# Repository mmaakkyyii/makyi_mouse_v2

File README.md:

# マッキーマウスv2
これはマッキーマウスの基板用リポジトリです  
ソフトは[こちら](https://github.com/mmaakkyyii/makyi_mouse_FW)

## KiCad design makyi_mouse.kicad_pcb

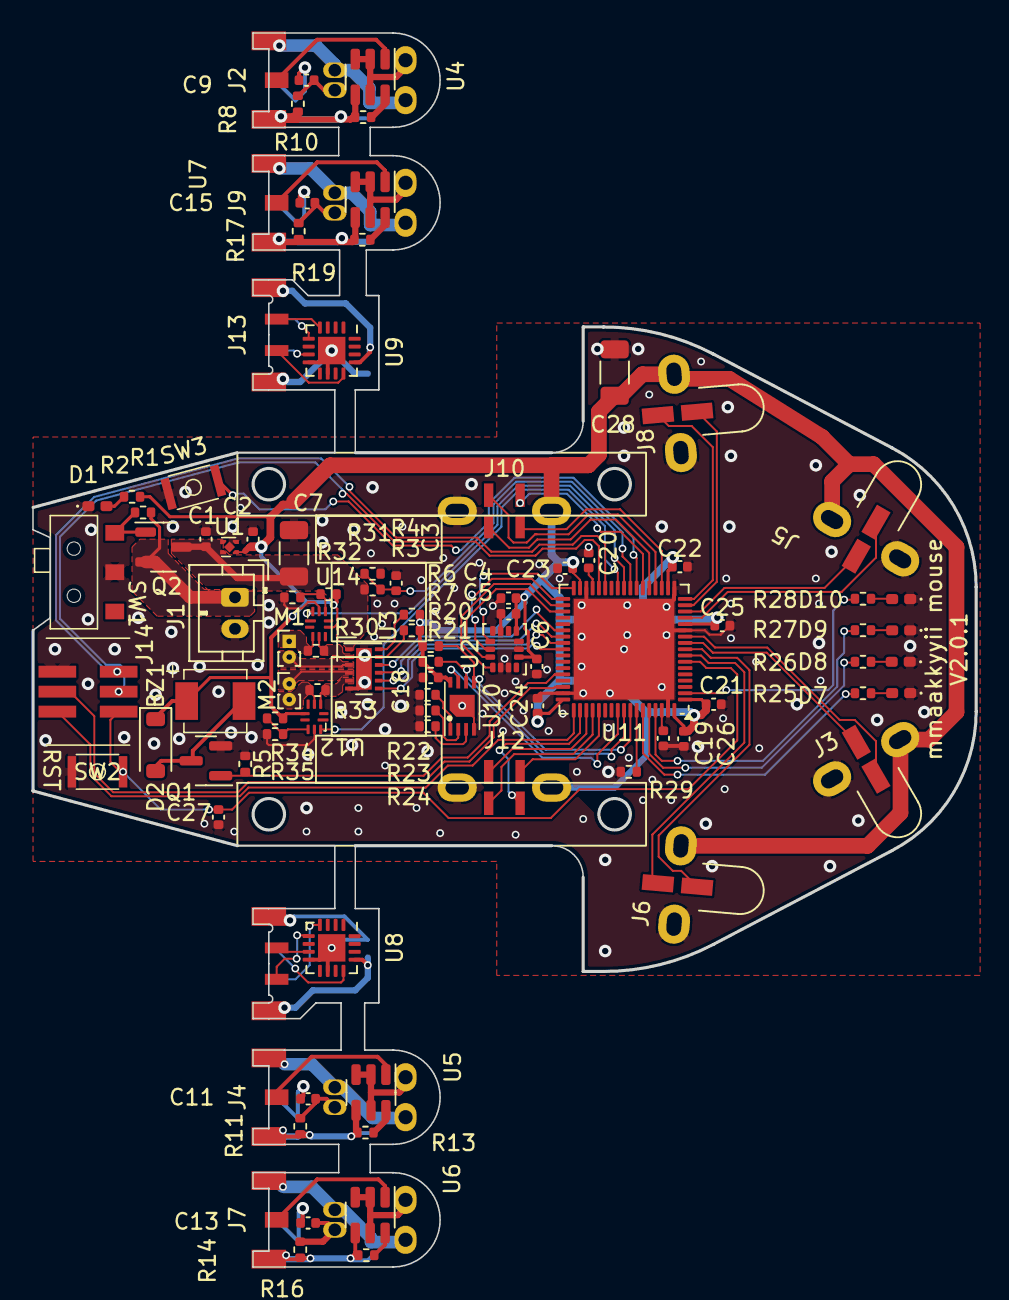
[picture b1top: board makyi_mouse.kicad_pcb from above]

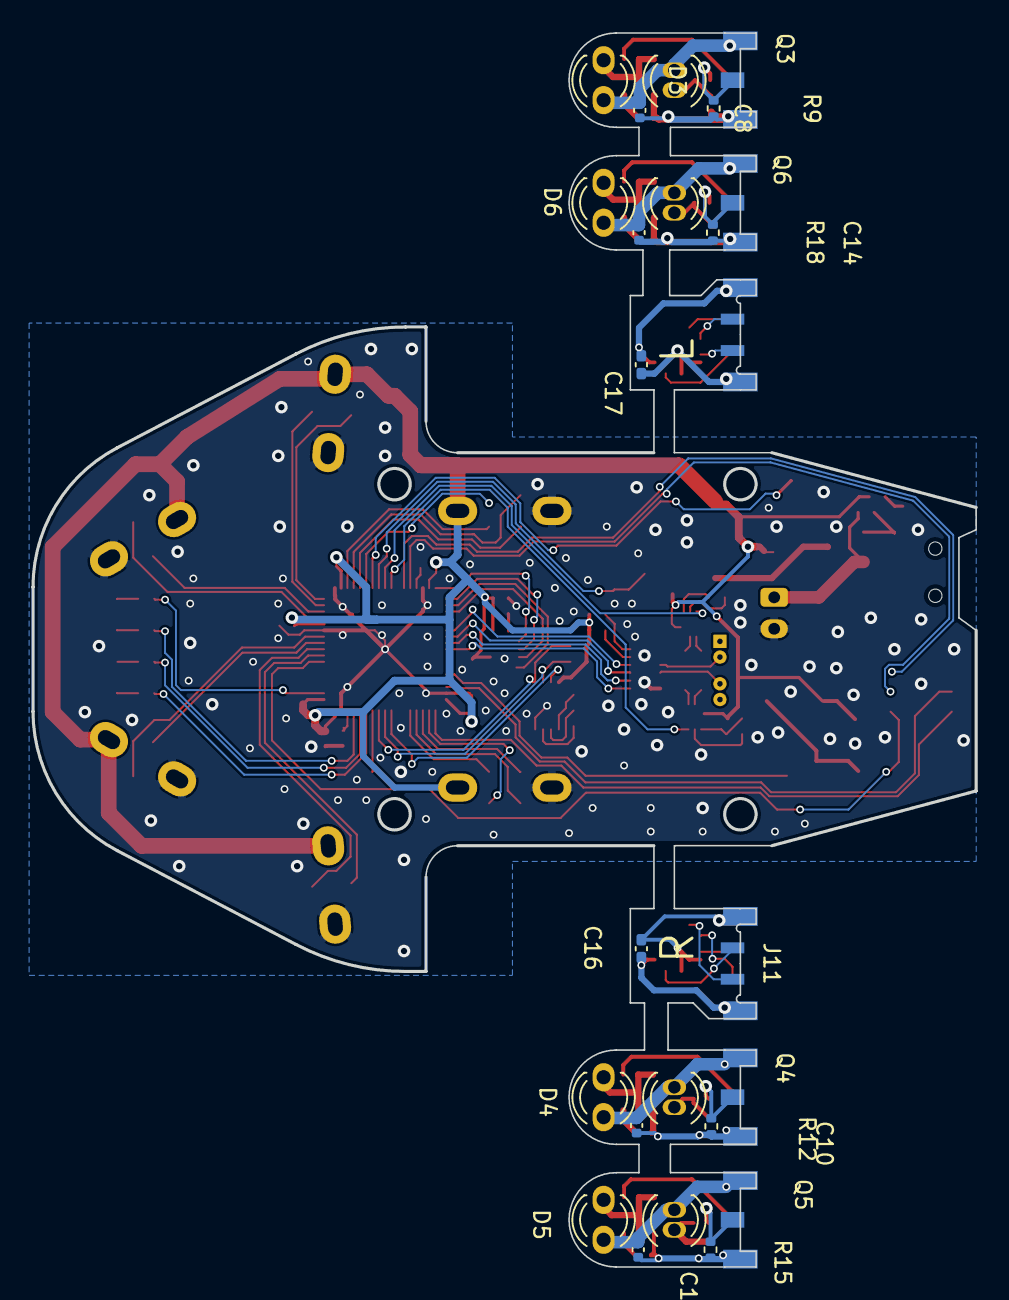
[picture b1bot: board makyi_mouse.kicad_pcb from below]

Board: 2 copper layers, 60.0 x 78.4 mm, 112 parts (19 on the bottom side), 108 nets.

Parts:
BZ1: SMT-0440-T-HT-R
C1, C2, C8, C10, C12, C14: 1u; C_0402_1005Metric
C3, C5, C9, C11, C13, C15, C18, C21, C22, C23, C24, C25, C26, C27: 0.1u; C_0402_1005Metric
C4, C19, C20: 2.2u; C_0402_1005Metric
C6: 0.01u; C_0402_1005Metric
C7, C28: 10u; C_1206_3216Metric
C16, C17: 0.1u; C_0402_1005Metric_Pad0.74x0.62mm_HandSolder
D1, D7, D8, D9, D10: LED; LED_0402_1005Metric_Pad0.77x0.64mm_HandSolder
D2: C258207; D_SOD-123
D3, D4, D5, D6: OSI5FU3A11C; LED
J1: Conn_01x02_Pin; JST_PH_B2B-PH-K_1x02_P2.00mm_Vertical
J2, J4, J7, J9: Conn_01x04_Pin; wall_sensor_board
J3, J5, J6, J8: Conn_01x04_Pin; wall_sensor_fp
J10, J12: Conn_01x06_Pin; enc_fp
J11, J13: Conn_01x06_Pin; enc_board
J14: 20021221-00006C4LF
M1, M2: Motor_DC; PinHeader_1x02_P1.00mm_Vertical
Q1: DMN63D8L-7; SOT-23
Q2: GSFC02A05; SOT-23-3
Q3, Q4, Q5, Q6: OP505A; LED_photo_tr
R1: 100k; R_0402_1005Metric
R2, R20, R21, R25, R26, R27, R28: 3.3k; R_0402_1005Metric
R3: 6.8k; R_0402_1005Metric
R4: 15k; R_0402_1005Metric
R5, R9, R12, R15, R18, R30, R31, R32, R33, R34, R35: 10k; R_0402_1005Metric
R6, R7, R22, R23, R24, R29: 0; R_0402_1005Metric
R8, R11, R14, R17: 1.5k; R_0402_1005Metric
R10, R13, R16, R19: 8.2; R_0402_1005Metric
SW1: AYZ0102AGRLC
SW2, SW3: C5143614
U1: NCP177AMX330TCG; XDFN4
U2: ICM-42688-P; LGA-14_3x2.5mm_P0.5mm_LayoutBorder3x4y
U3: DRV8836DSSR; WSON-12-1EP_3x2mm_P0.5mm_EP1x2.65
U4, U5, U6, U7: BCR421UW6-7; SOT-23-6
U8, U9: MA730; QFN-16-1EP_3x3mm_P0.5mm_EP1.75x1.75mm
U10: v; LCC-8P-M04
U11: STM32H573RIVx; QFN-68-1EP_8x8mm_P0.4mm_EP6.4x6.4mm
U12, U14: INA210; UQFN-10

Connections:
+3.3V: BZ1.1 (-), C2.1, C4.1, C5.1, C6.1, C18.1, C21.1, C22.1, C23.1, C24.1, C25.1, C26.1, C28.1, D2.1 (K), J3.4, J5.4, J6.4, J8.4, J10.1, J12.1, R2.1, R6.2, R7.2, R20.1, R21.1, R31.1, R34.1, U1.1 (OUT), U2.5 (VDDIO), U2.8 (VDD), U10.8 (VDD), U11.1 (VBAT), U11.13 (VDDA), U11.19 (VDD), U11.33 (VDD), U11.51 (VDD), U11.68 (VDD), U12.6 (V+), U14.6 (V+)
/AIN1: U3.10 (AIN1/APHASE), U11.40 (PC6)
/AIN2: U3.9 (AIN2/AENBL), U11.41 (PC7)
/BATT_ADC: C3.1, R3.2, R4.1, U11.25 (PC5)
/BIN1: U3.8 (BIN1/BPHASE), U11.42 (PC8)
/BIN2: U3.7 (BIN2/BENBL), U11.43 (PC9)
/BUZZER: Q1.1 (G), R5.2, U11.47 (PA11)
/DEBUG_RX: J14.3, U11.30 (PB11)
/DEBUG_TX: J14.5, U11.29 (PB10)
/ENC_L_CS: J10.4, U11.20 (PA4)
/ENC_L_MISO: J10.5, U11.22 (PA6)
/ENC_L_MOSI: J10.2, U11.23 (PA7)
/ENC_L_SCLK: J10.3, U11.21 (PA5)
/ENC_R_CS: J12.4, U11.53 (PA15(JTDI))
/ENC_R_MISO: J12.5, U11.55 (PC11)
/ENC_R_MOSI: J12.2, U11.56 (PC12)
/ENC_R_SCLK: J12.3, U11.54 (PC10)
/Flash_SCL: R21.2, U10.6 (SCL), U11.60 (PB6)
/Flash_SDA: R20.2, U10.5 (SDA), U11.61 (PB7)
/Flash_WP: U10.7 (WP), U11.59 (PB5)
/IMU_CS: U2.12 (AP_CS), U11.34 (PB12)
/IMU_MISO: U2.1 (AP_SDO/AP_AD0), U11.36 (PB14)
/IMU_MOSI: U2.14 (AP_SDA/AP_SDIO/AP_SDI), U11.37 (PB15)
/IMU_SCLK: U2.13 (AP_SCLK/AP_SCLK), U11.35 (PB13)
/I_left: U11.26 (PB0), U14.10
/I_right: U11.27 (PB1), U12.10
/LED1: R25.1, U11.63 (PB8)
/LED2: R26.1, U11.64 (PB9)
/LED3: R27.1, U11.65 (PE0)
/LED4: R28.1, U11.2 (PC13)
/LED_FL: J8.1, U11.17 (PA3)
/LED_FR: J6.1, U11.8 (PC0)
/LED_L: J5.1, U11.15 (PA1)
/LED_R: J3.1, U11.10 (PC2)
/NRST: C27.1, J14.1, SW2.2, U11.7 (NRST)
/SENSOR_FL: J8.2, U11.16 (PA2)
/SENSOR_FR: J6.2, U11.9 (PC1)
/SENSOR_L: J5.2, U11.14 (PA0)
/SENSOR_R: J3.2, U11.11 (PC3)
/SWCLK: J14.2, U11.52 (PA14(JTCK)
/SWDIO: J14.4, U11.49 (PA13(JTMS)
/USER_SW: SW3.2, U11.24 (PC4)
/encorder1/CS: J13.4, U9.5 (~CS)
/encorder1/MISO: J13.5, U9.7 (MISO)
/encorder1/MOSI: J13.2, U9.4 (MOSI)
/encorder1/SCLK: J13.3, U9.12 (SCLK)
/encorder/CS: J11.4, U8.5 (~CS)
/encorder/MISO: J11.5, U8.7 (MISO)
/encorder/MOSI: J11.2, U8.4 (MOSI)
/encorder/SCLK: J11.3, U8.12 (SCLK)
/wall_sensor1/ENC_3.3V: C10.1, D4.2 (A), J4.4, Q4.1 (C)
/wall_sensor1/ENC_GND: C10.2, J4.3, R11.2, R12.2, R13.1, U5.4 (GND)
/wall_sensor1/ENC_LED: J4.1, U5.1 (EN)
/wall_sensor1/ENC_OUT: C11.1, J4.2, R12.1
/wall_sensor2/ENC_3.3V: C12.1, D5.2 (A), J7.4, Q5.1 (C)
/wall_sensor2/ENC_GND: C12.2, J7.3, R14.2, R15.2, R16.1, U6.4 (GND)
/wall_sensor2/ENC_LED: J7.1, U6.1 (EN)
/wall_sensor2/ENC_OUT: C13.1, J7.2, R15.1
/wall_sensor3/ENC_3.3V: C14.1, D6.2 (A), J9.4, Q6.1 (C)
/wall_sensor3/ENC_GND: C14.2, J9.3, R17.2, R18.2, R19.1, U7.4 (GND)
/wall_sensor3/ENC_LED: J9.1, U7.1 (EN)
/wall_sensor3/ENC_OUT: C15.1, J9.2, R18.1
/wall_sensor/ENC_3.3V: C8.1, D3.2 (A), J2.4, Q3.1 (C)
/wall_sensor/ENC_GND: C8.2, J2.3, R8.2, R9.2, R10.1, U4.4 (GND)
/wall_sensor/ENC_LED: J2.1, U4.1 (EN)
/wall_sensor/ENC_OUT: C9.1, J2.2, R9.1
GND: C1.2, C2.2, C3.2, C4.2, C5.2, C6.2, C7.2, C18.2, C19.2, C20.2, C21.2, C22.2, C23.2, C24.2, C25.2, C26.2, C27.2, C28.2, D1.1 (K), D7.1 (K), D8.1 (K), D9.1 (K), D10.1 (K), J1.2, J3.3, J5.3, J6.3, J8.3, J10.6, J12.6, J14.6, Q1.2 (S), R4.2, R5.1, R22.2, R23.2, R24.2, R29.2, R32.1, R35.1, SW1.2 (B), SW2.1, SW3.1, U1.2 (GND), U2.2 (RESV), U2.3 (RESV), U2.6 (GND), U2.7 (RESV), U2.10 (RESV), U2.11 (RESV), U3.6 (GND), U3.13 (EPAD), U10.4 (VSS), U10.9 (VSS), U11.12 (VSSA), U11.18 (VSS), U11.32 (VSS), U11.50 (VSS), U11.67 (VSS), U11.69 (VSS), U12.9 (GND), U14.9 (GND)
unnamed: BZ1.2 (+), D2.2 (A), Q1.3 (D)
unnamed: C19.1, U11.66 (VCAP)
unnamed: C20.1, U11.31 (VCAP)
unnamed: D1.2 (A), R2.2
unnamed: D3.1 (K), U4.2 (OUT), U4.3 (OUT), U4.5 (OUT)
unnamed: D4.1 (K), U5.2 (OUT), U5.3 (OUT), U5.5 (OUT)
unnamed: D5.1 (K), U6.2 (OUT), U6.3 (OUT), U6.5 (OUT)
unnamed: D6.1 (K), U7.2 (OUT), U7.3 (OUT), U7.5 (OUT)
unnamed: D7.2 (A), R25.2
unnamed: D8.2 (A), R26.2
unnamed: D9.2 (A), R27.2
unnamed: D10.2 (A), R28.2
unnamed: J1.1, Q2.2 (S), R1.1
unnamed: C16.1, J11.1, U8.13 (VDD)
unnamed: C16.2, J11.6, U8.8 (GND), U8.10 (TEST), U8.17 (PAD)
unnamed: C17.1, J13.1, U9.13 (VDD)
unnamed: C17.2, J13.6, U9.8 (GND), U9.10 (TEST), U9.17 (PAD)
unnamed: M1.1 (+), R30.1, U14.3 (+)
unnamed: M1.2 (-), U3.3 (AOUT2)
unnamed: M2.1 (+), U3.4 (BOUT1)
unnamed: M2.2 (-), R33.2, U12.4 (-)
unnamed: Q2.1 (G), R1.2, SW1.1 (A)
unnamed: C9.2, Q3.2 (E), R8.1
unnamed: C11.2, Q4.2 (E), R11.1
unnamed: C13.2, Q5.2 (E), R14.1
unnamed: C15.2, Q6.2 (E), R17.1
unnamed: R7.1, U3.11 (MODE)
unnamed: R6.1, U3.12 (nSLEEP)
unnamed: R10.2, U4.6 (R_EXT)
unnamed: R13.2, U5.6 (R_EXT)
unnamed: R16.2, U6.6 (R_EXT)
unnamed: R19.2, U7.6 (R_EXT)
unnamed: R22.1, U10.1 (A0)
unnamed: R23.1, U10.2 (A1)
unnamed: R24.1, U10.3 (A2)
unnamed: R29.1, U11.62 (BOOT0)
unnamed: R33.1, U3.5 (BOUT2), U12.3 (+)
unnamed: R34.2, R35.2, U12.8 (REF)
unnamed: R30.2, U3.2 (AOUT1), U14.4 (-)
unnamed: R31.2, R32.2, U14.8 (REF)
VCC: C1.1, C7.1, Q2.3 (D), R3.1, U1.3 (EN), U1.4 (IN), U3.1 (VCC)

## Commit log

2024-06-29 写真追加
2024-06-29 画像追加
2024-06-29 壁センサ修正
2024-07-11 画像修正
